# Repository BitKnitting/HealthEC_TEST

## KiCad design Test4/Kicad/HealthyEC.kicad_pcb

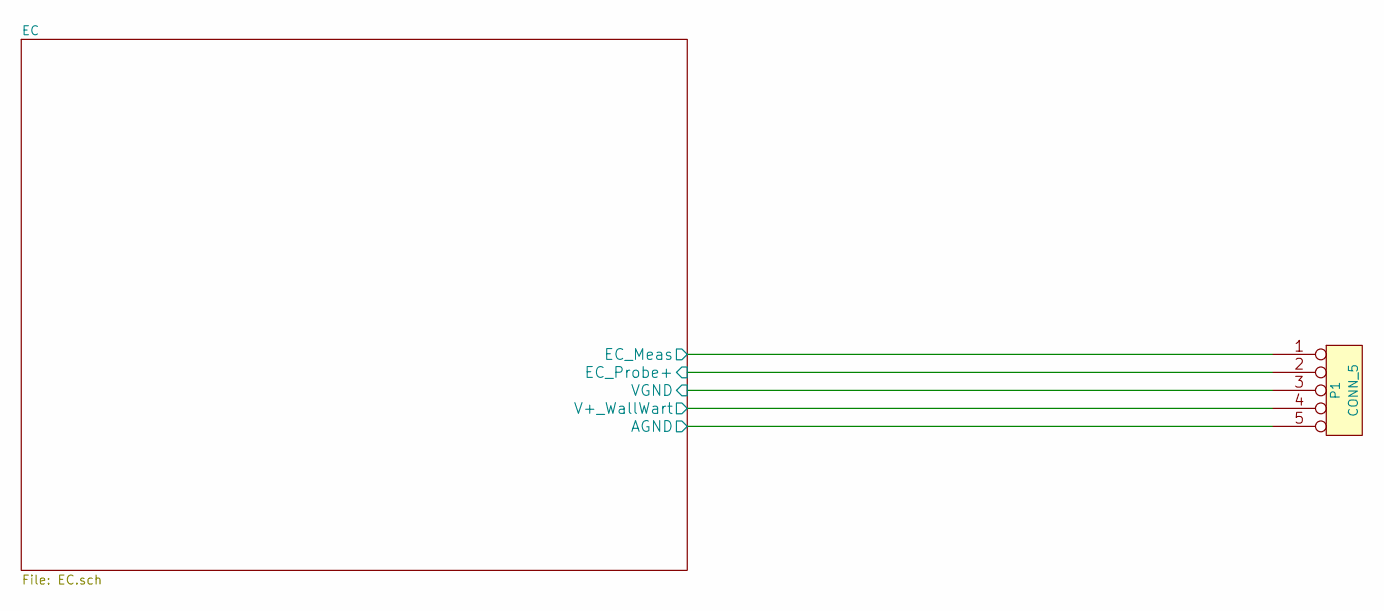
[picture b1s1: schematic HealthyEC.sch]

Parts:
P1: CONN_5

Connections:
/EC/EC_Meas: P1.1; also elsewhere on the board
/EC/EC_Probe+: P1.2; also elsewhere on the board
/EC/V+_WallWart: P1.4; also elsewhere on the board
/EC/VGND: P1.3; also elsewhere on the board
AGND: P1.5; also elsewhere on the board

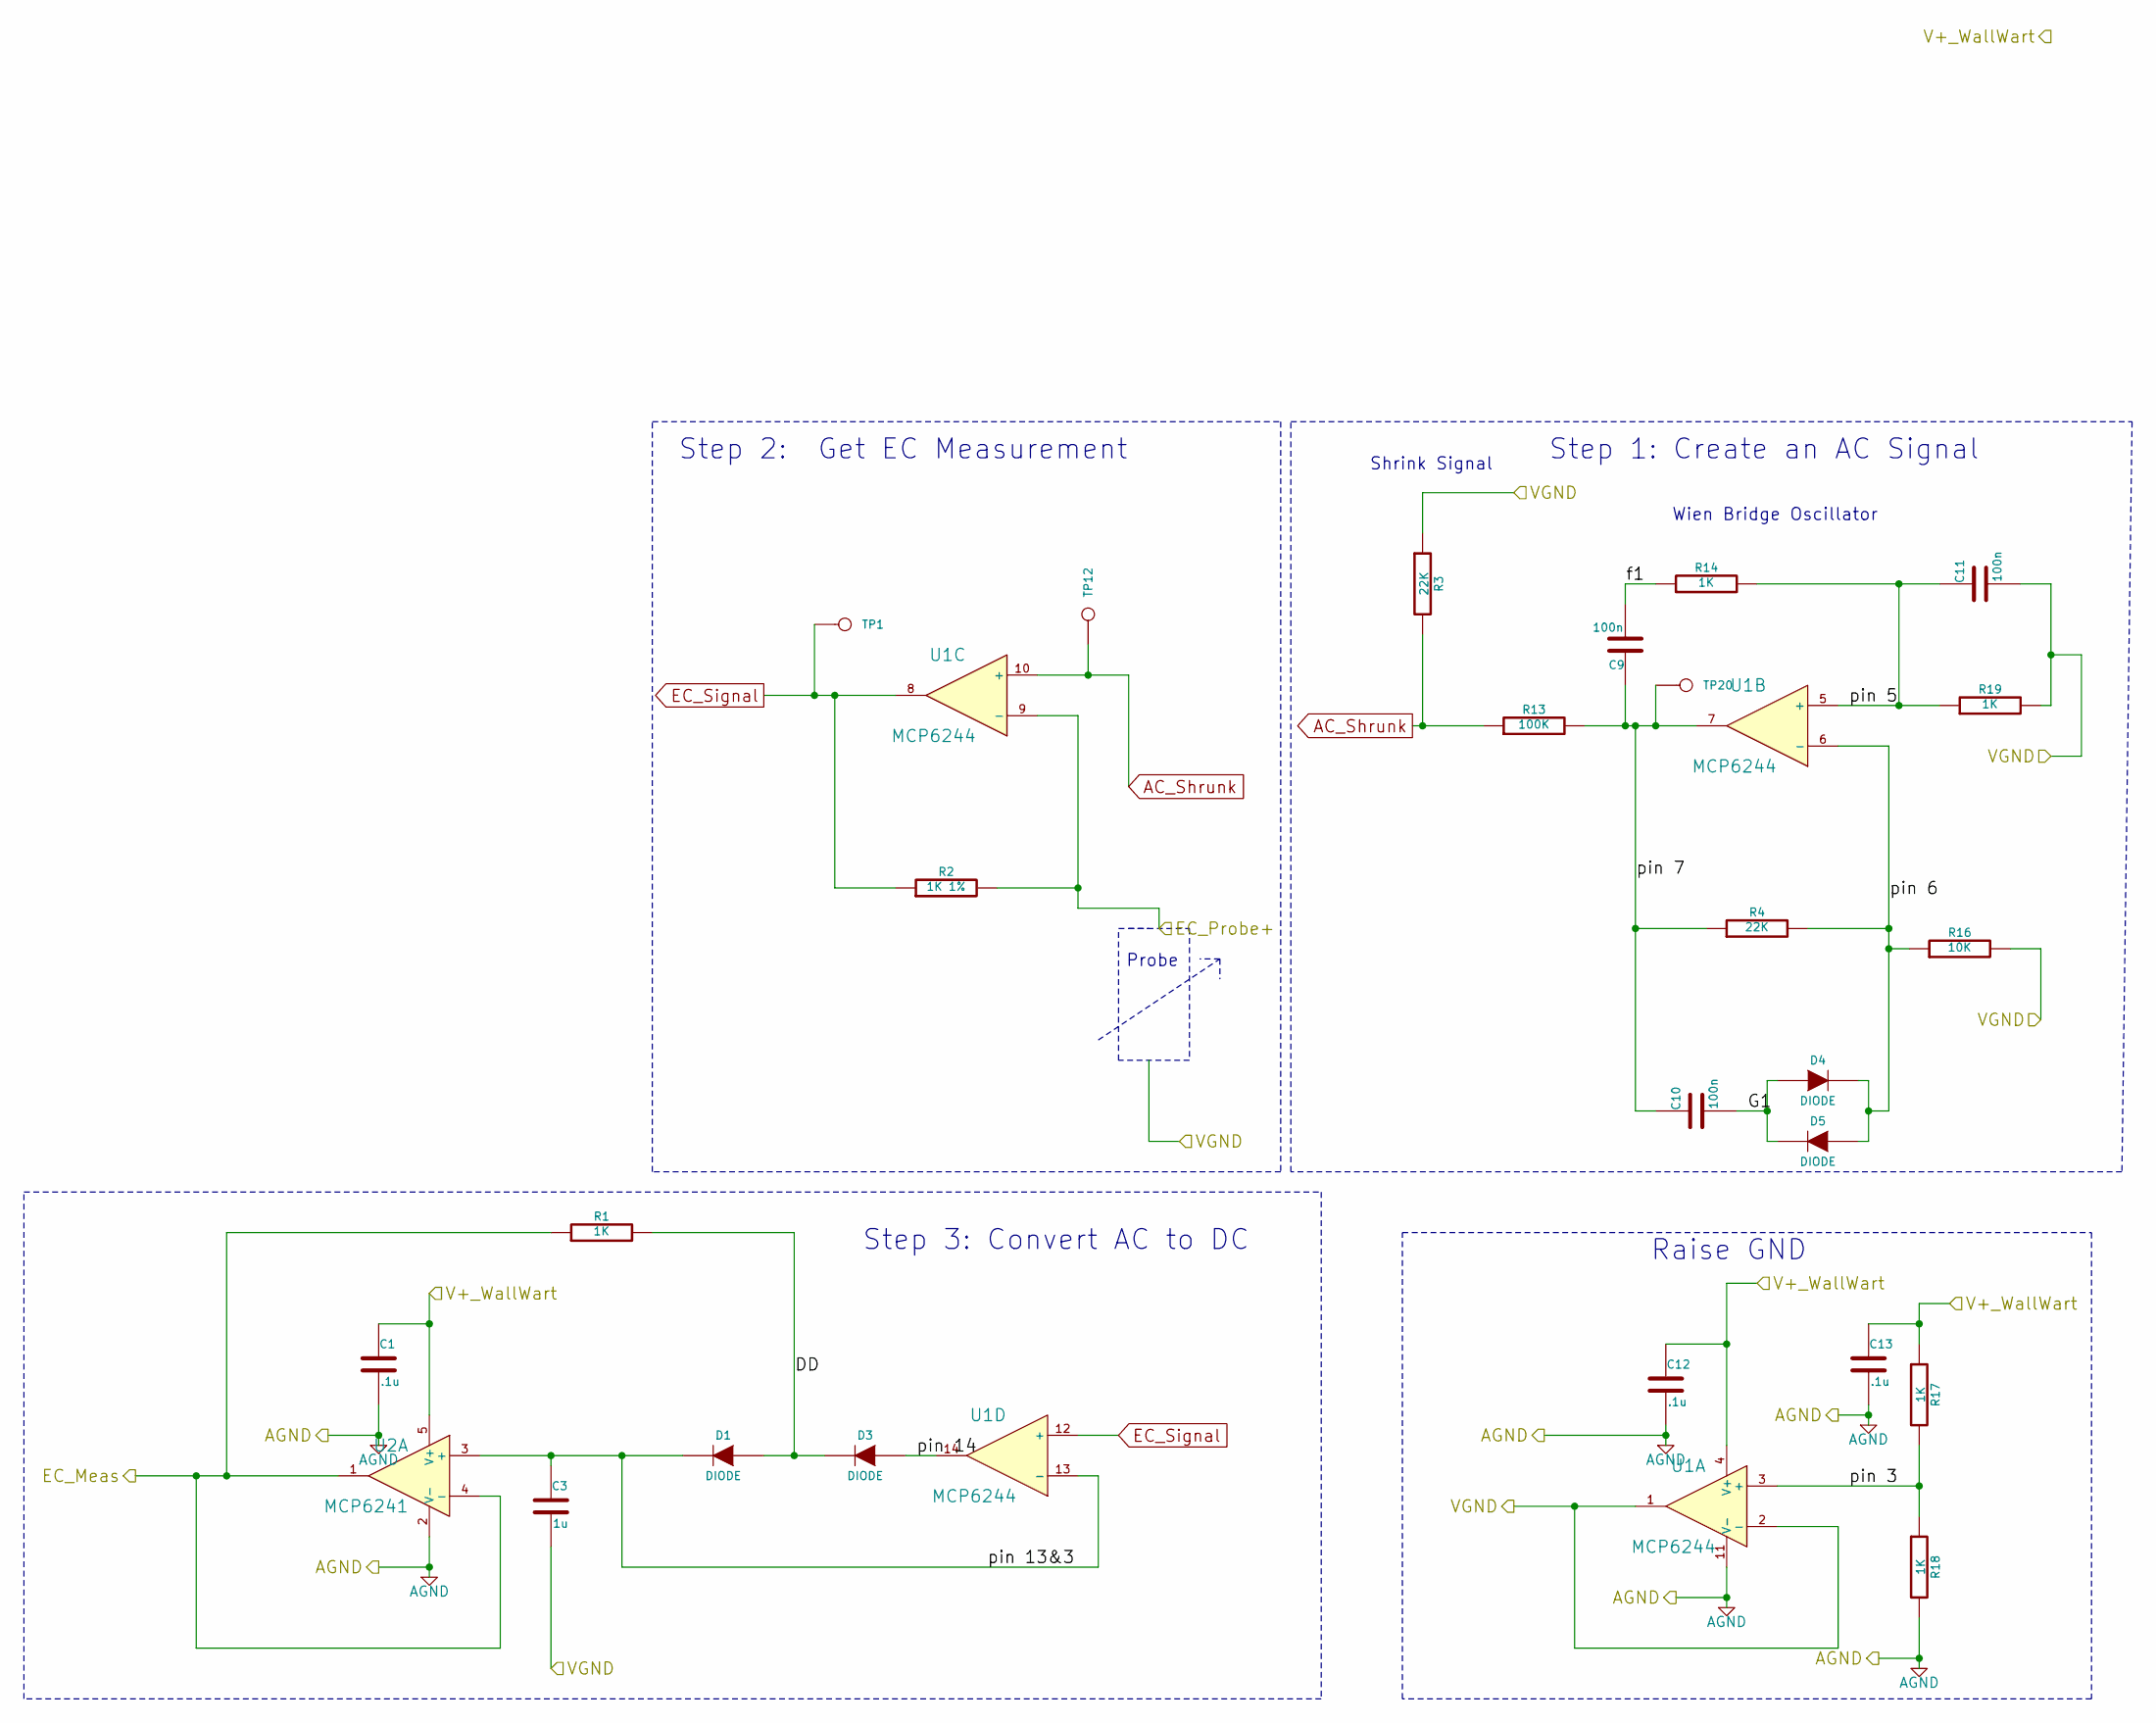
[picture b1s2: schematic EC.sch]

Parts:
C1, C12, C13: .1u
C3: 1u
C9, C10, C11: 100n
D1, D3, D4, D5: DIODE
R1, R14, R17, R18, R19: 1K
R2: 1K 1%
R3, R4: 22K
R13: 100K
R16: 10K
TP1, TP12, TP20: CONN_1
U1: MCP6244
U2: MCP6241

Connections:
/EC/DD: D1.1 (A), D3.2 (K), R1.2
/EC/EC_Meas: R1.1, U2.1, U2.4 (-); also elsewhere on the board
/EC/EC_Probe+: R2.2, U1.9 (-); also elsewhere on the board
/EC/G1: C10.2, D4.1 (A), D5.2 (K)
/EC/V+_WallWart: C1.1, C12.1, C13.1, R17.1, U1.4 (V+), U2.5 (V+); also elsewhere on the board
/EC/VGND: C3.2, C11.2, R3.1, R16.2, R19.2, U1.1, U1.2 (-); also elsewhere on the board
/EC/f1: C9.2, R14.1
/EC/pin 3: R17.2, R18.1, U1.3 (+)
/EC/pin 5: C11.1, R14.2, R19.1, U1.5 (+)
/EC/pin 6: D4.2 (K), D5.1 (A), R4.2, R16.1, U1.6 (-)
/EC/pin 7: C9.1, C10.1, R4.1, R13.2, TP20.1, U1.7
/EC/pin 13&3: C3.1, D1.2 (K), U1.13 (-), U2.3 (+)
/EC/pin 14: D3.1 (A), U1.14
AC_Shrunk: R3.2, R13.1, TP12.1, U1.10 (+)
AGND: C1.2, C12.2, C13.2, R18.2, U1.11 (V-), U2.2 (V-); also elsewhere on the board
EC_Signal: R2.1, TP1.1, U1.8, U1.12 (+)

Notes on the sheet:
Wien Bridge Oscillator
Shrink Signal
Step 1: Create an AC Signal
Raise GND
Probe
Step 2: Get EC Measurement
Step 3: Convert AC to DC

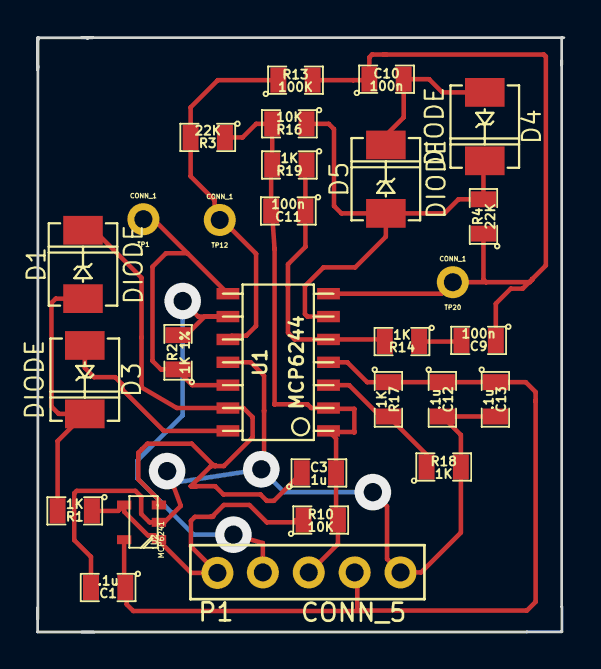
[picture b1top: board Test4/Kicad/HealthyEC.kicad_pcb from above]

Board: 2 copper layers, 29.3 x 33.0 mm, 28 parts (0 on the bottom side), 16 nets.

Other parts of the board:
R10: 10K; SM0805

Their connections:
/EC/EC_Meas: R10.1; also elsewhere on the board
/EC/VGND: R10.2; also elsewhere on the board

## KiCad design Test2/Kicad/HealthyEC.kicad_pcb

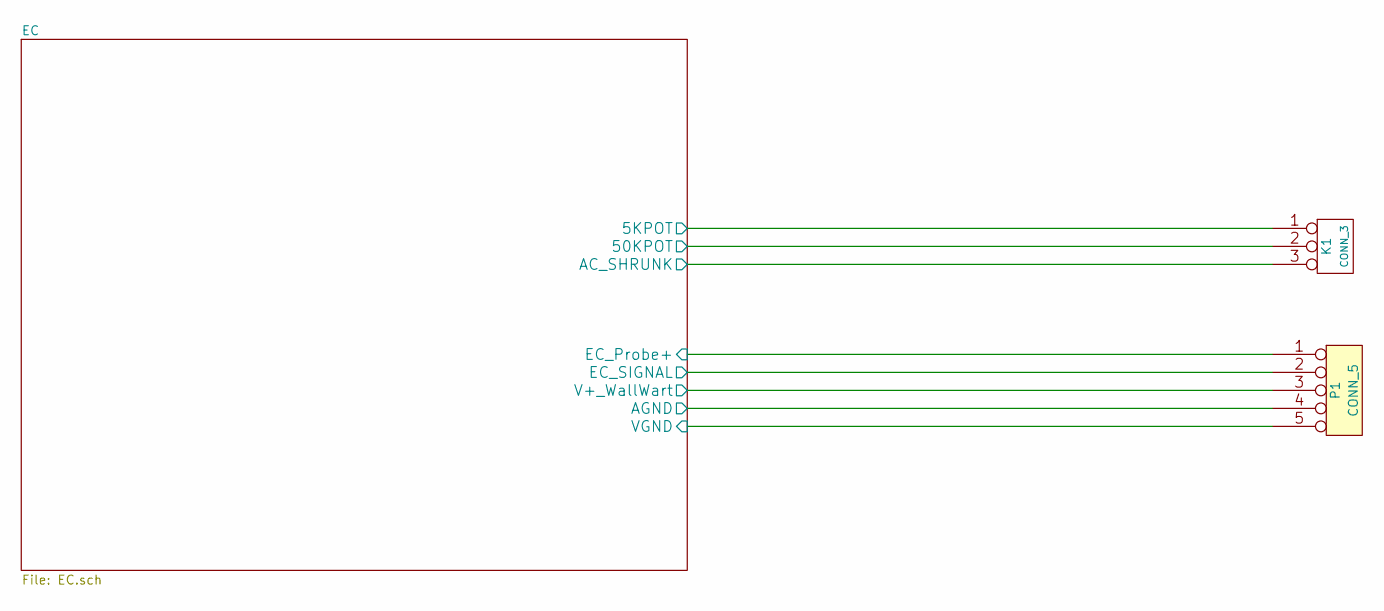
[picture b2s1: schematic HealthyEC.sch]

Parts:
K1: CONN_3
P1: CONN_5

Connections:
/EC/5KPOT: K1.1; also elsewhere on the board
/EC/50KPOT: K1.2 (PM); also elsewhere on the board
/EC/EC_Probe+: P1.1; also elsewhere on the board
/EC/V+_WallWart: P1.3; also elsewhere on the board
/EC/VGND: P1.5; also elsewhere on the board
AC_Shrunk: K1.3; also elsewhere on the board
AGND: P1.4; also elsewhere on the board
EC_Signal: P1.2; also elsewhere on the board

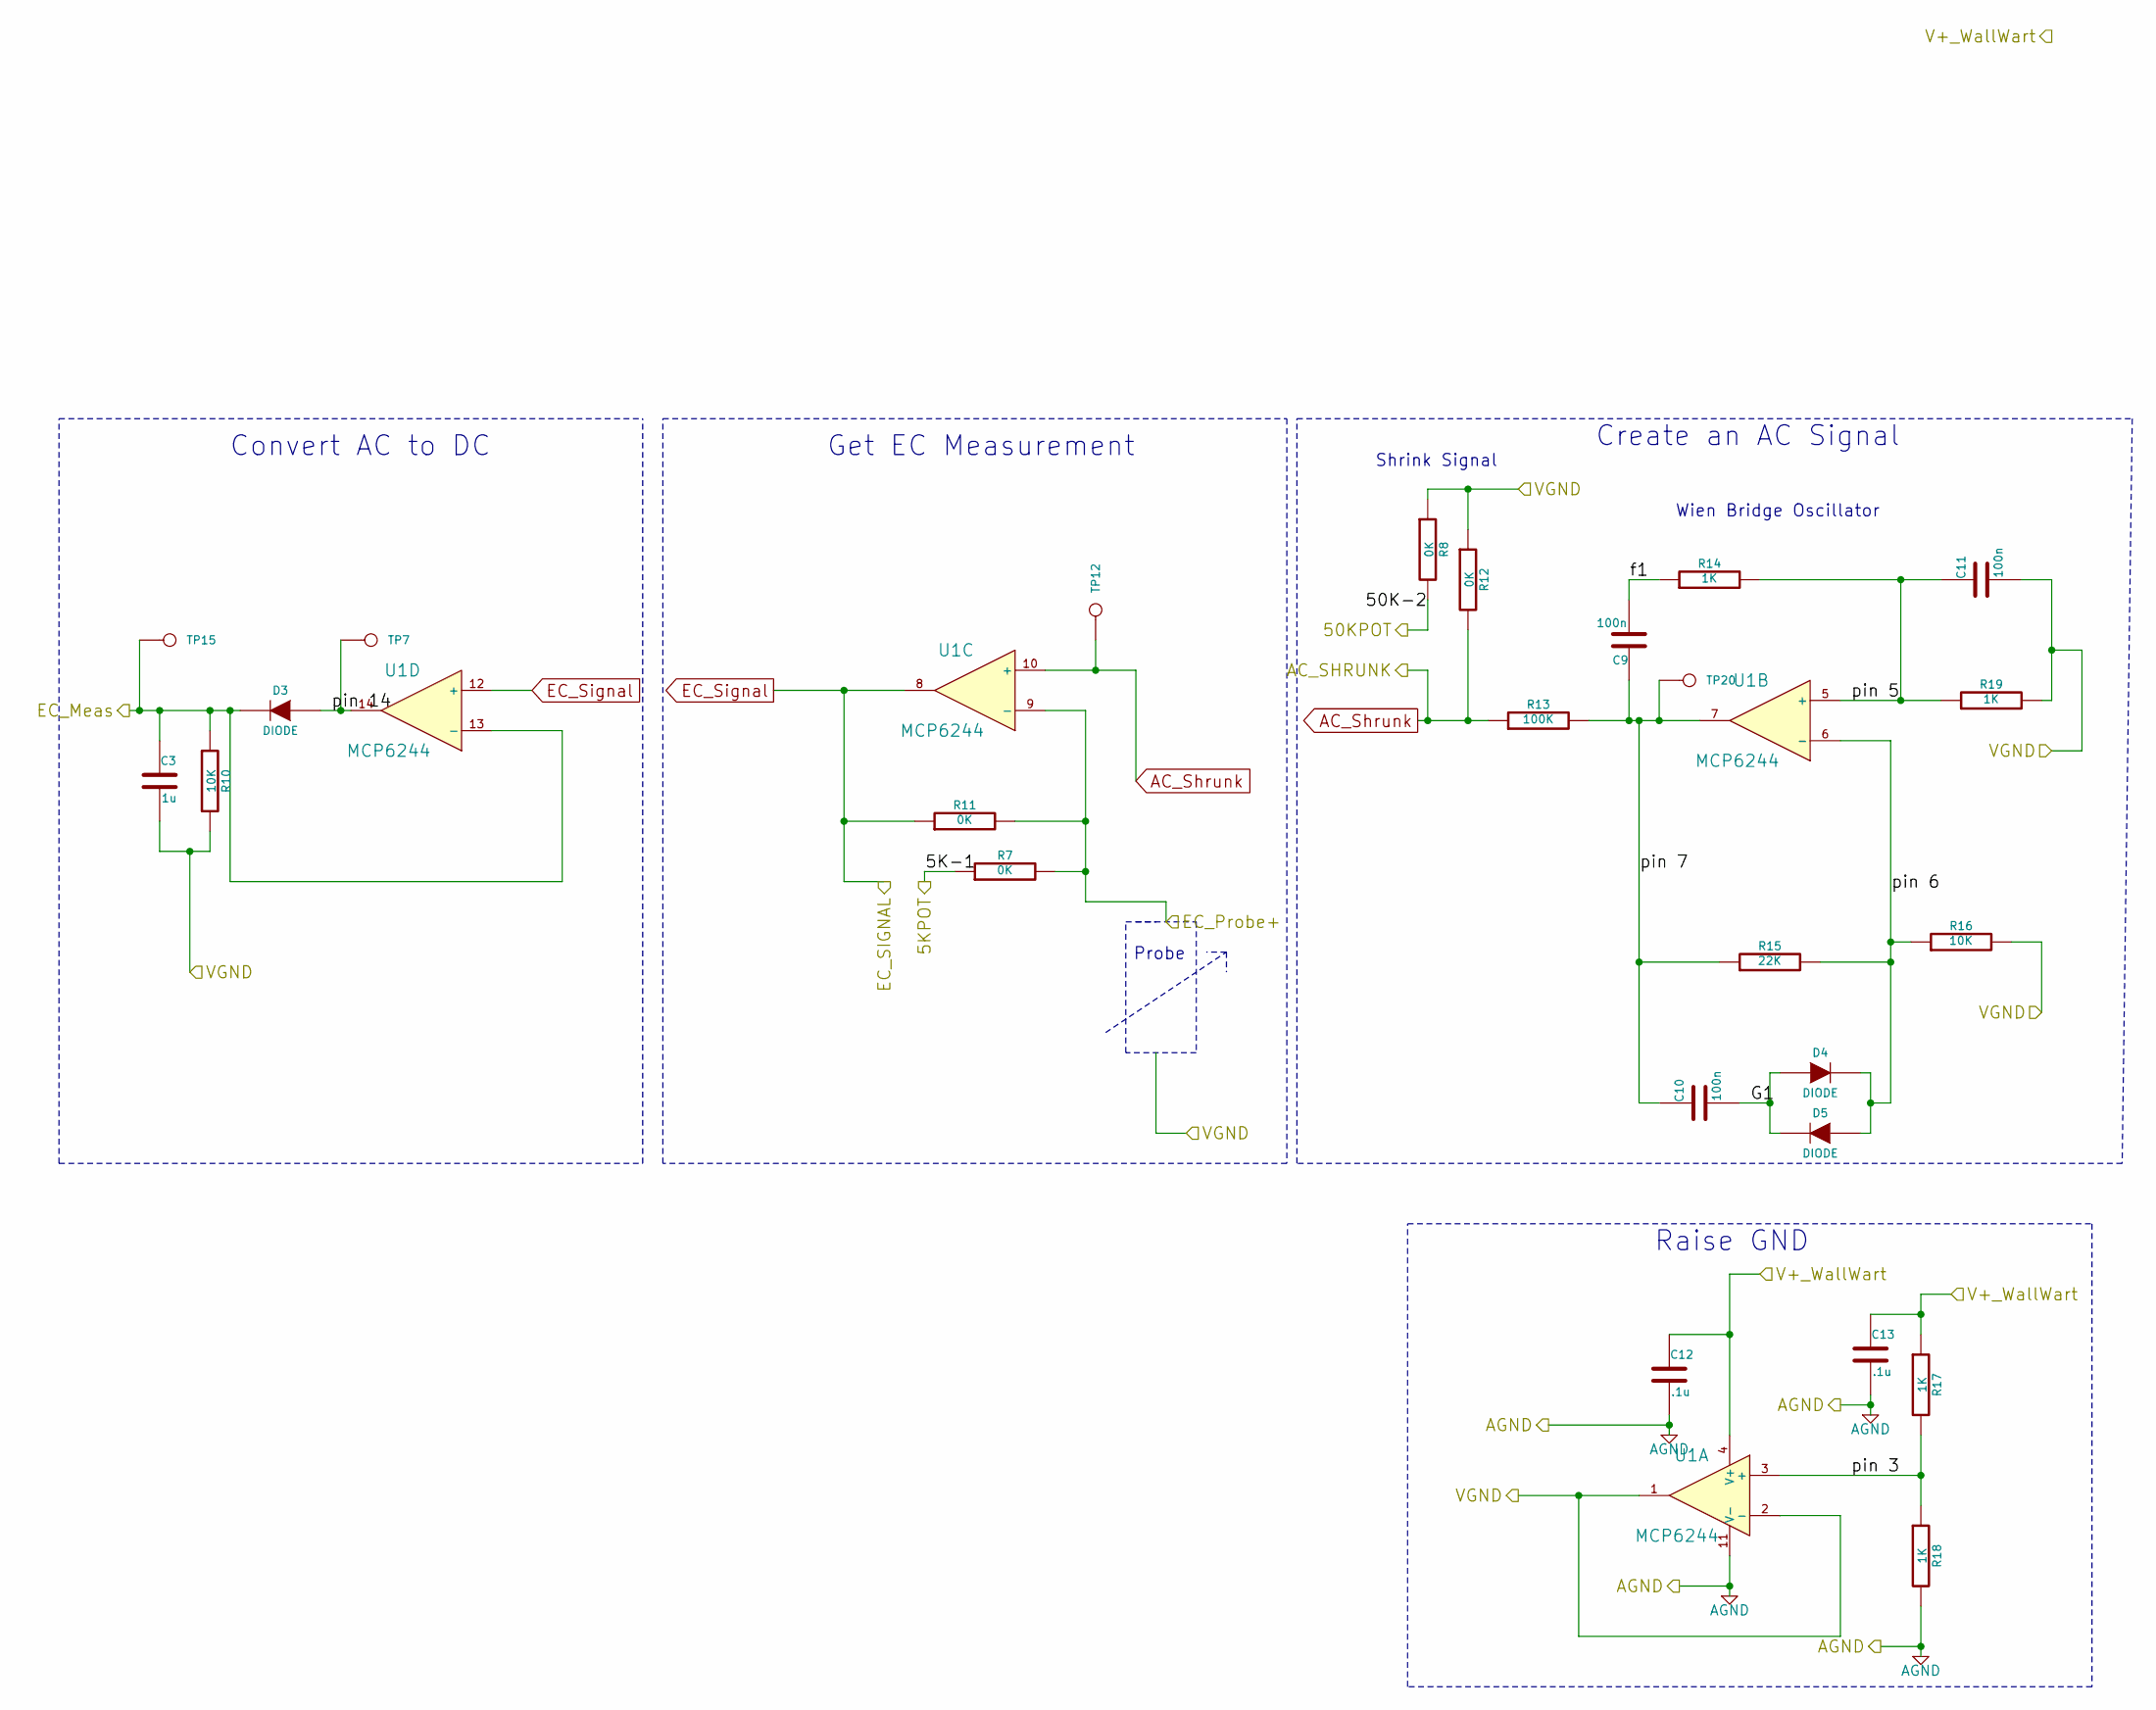
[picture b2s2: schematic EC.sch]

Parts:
C3: 1u
C9, C10, C11: 100n
C12, C13: .1u
D3, D4, D5: DIODE
R7, R8, R11, R12: 0K
R10, R16: 10K
R13: 100K
R14, R17, R18, R19: 1K
R15: 22K
TP7, TP12, TP15, TP20: CONN_1
U1: MCP6244

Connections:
/EC/5KPOT: R7.1; also elsewhere on the board
/EC/50KPOT: R8.2; also elsewhere on the board
/EC/EC_Meas: C3.1, D3.2 (K), R10.1, TP15.1, U1.13 (-)
/EC/EC_Probe+: R7.2, R11.2, U1.9 (-); also elsewhere on the board
/EC/G1: C10.2, D4.1 (A), D5.2 (K)
/EC/V+_WallWart: C12.1, C13.1, R17.1, U1.4 (V+); also elsewhere on the board
/EC/VGND: C3.2, C11.2, R8.1, R10.2, R12.1, R16.2, R19.2, U1.1, U1.2 (-); also elsewhere on the board
/EC/f1: C9.2, R14.1
/EC/pin 3: R17.2, R18.1, U1.3 (+)
/EC/pin 5: C11.1, R14.2, R19.1, U1.5 (+)
/EC/pin 6: D4.2 (K), D5.1 (A), R15.2, R16.1, U1.6 (-)
/EC/pin 7: C9.1, C10.1, R13.2, R15.1, TP20.1, U1.7
/EC/pin 14: D3.1 (A), TP7.1, U1.14
AC_Shrunk: R12.2, R13.1, TP12.1, U1.10 (+); also elsewhere on the board
AGND: C12.2, C13.2, R18.2, U1.11 (V-); also elsewhere on the board
EC_Signal: R11.1, U1.8, U1.12 (+); also elsewhere on the board

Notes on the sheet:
Wien Bridge Oscillator
Shrink Signal
Create an AC Signal
Raise GND
Probe
Get EC Measurement
Convert AC to DC

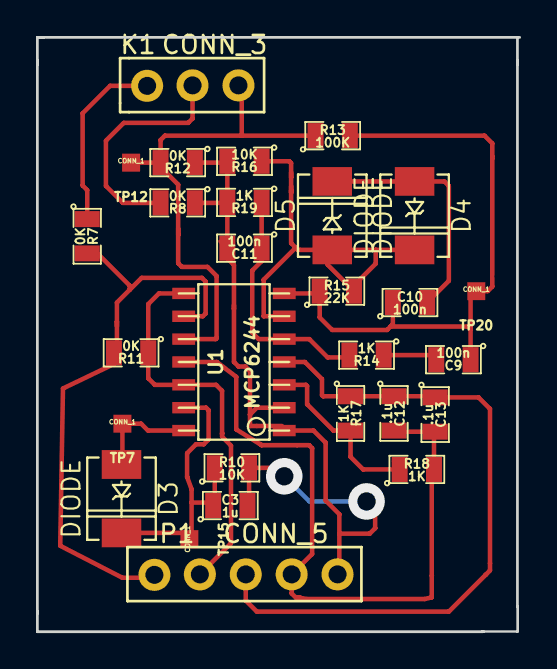
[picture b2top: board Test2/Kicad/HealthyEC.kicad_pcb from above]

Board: 2 copper layers, 26.8 x 33.0 mm, 28 parts (0 on the bottom side), 16 nets.

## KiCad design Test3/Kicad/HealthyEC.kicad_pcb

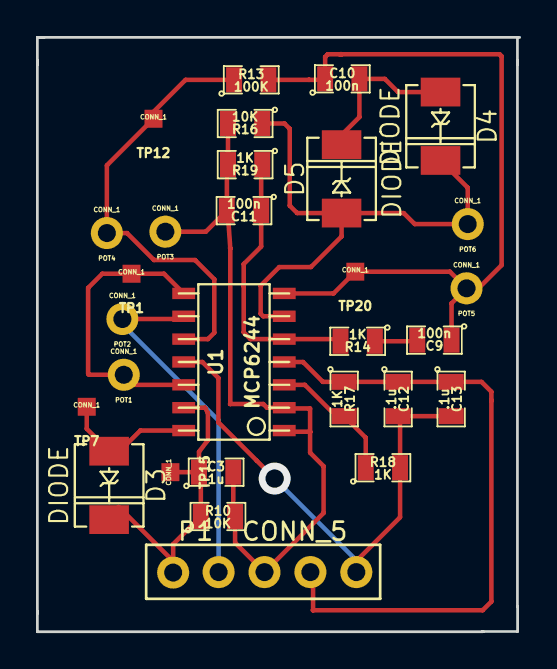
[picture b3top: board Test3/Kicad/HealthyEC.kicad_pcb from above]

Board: 2 copper layers, 26.8 x 33.0 mm, 29 parts (0 on the bottom side), 14 nets.

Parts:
C3: 1u; SM0805
C9, C10, C11: 100n; SM0805
C12, C13: .1u; SM0805
D3, D4, D5: DIODE; DO-214AC(SMA)
P1: CONN_5; LB_CONN_5
POT1, POT2, POT3, POT4, POT5, POT6: CONN_1; LB_CONN_1
R10, R16: 10K; SM0805
R13: 100K; SM0805
R14, R17, R18, R19: 1K; SM0805
TP1, TP7, TP12, TP15, TP20: CONN_1; LB_TestPoint
U1: MCP6244; so-14

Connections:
/EC/EC_Meas: C3.1, D3.2, P1.1, R10.1, TP15.1, U1.13
/EC/EC_Probe+: P1.2, POT2.1, U1.9
/EC/G1: C10.2, D4.1, D5.2
/EC/V+_WallWart: C12.1, C13.1, P1.4, R17.1, U1.4
/EC/VGND: C3.2, C11.2, P1.3, POT3.1, R10.2, R16.2, R19.2, U1.1, U1.2
/EC/f1: C9.2, R14.1
/EC/pin 3: R17.2, R18.1, U1.3
/EC/pin 5: C11.1, R14.2, R19.1, U1.5
/EC/pin 6: D4.2, D5.1, POT6.1, R16.1, U1.6
/EC/pin 7: C9.1, C10.1, POT5.1, R13.2, TP20.1, U1.7
/EC/pin 14: D3.1, TP7.1, U1.14
AC_Shrunk: POT4.1, R13.1, TP12.1, U1.10
AGND: C12.2, C13.2, P1.5, R18.2, U1.11
EC_Signal: POT1.1, TP1.1, U1.8, U1.12

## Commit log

2014-11-17 added test 2
2014-11-29 updating to most recent after successful initial tests
2014-11-29 clean up
2014-12-09 adding Test 4
2014-12-10 fixed mistake in schematic/layout for AD to DC conversion
2014-12-11 fixed track to nowhere on back layer
